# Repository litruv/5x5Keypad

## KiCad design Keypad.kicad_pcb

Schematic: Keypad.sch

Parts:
C1, C2: 22pF; C_0805_2012Metric_Pad1.15x1.40mm_HandSolder
C3, C5, C6, C7, C8, C9, C10, C11, C12, C13, C14, C15, C16: 0.1uF; C_0805_2012Metric_Pad1.15x1.40mm_HandSolder
C4: 1uF; C_0805_2012Metric_Pad1.15x1.40mm_HandSolder
D4, D5, D6, D7, D8, D9, D10, D11, D12, D13, D14, D15: WS2812B; LED_WS2812B_PLCC4_5.0x5.0mm_P3.2mm
F1: Polyfuse; Fuse_1206_3216Metric_Pad1.42x1.75mm_HandSolder
J1: AVR-ISP-6; PinHeader_2x03_P2.54mm_Vertical
Q1: Q_NPN_BCE; SOT-223-3_TabPin2
R1: 10K; R_0805_2012Metric_Pad1.15x1.40mm_HandSolder
R3, R4: 22; R_0805_2012Metric_Pad1.15x1.40mm_HandSolder
R6: 1.5k; R_0805_2012Metric_Pad1.15x1.40mm_HandSolder
SW1: SW_Push; CandK_6x6mm_Tactile
TRRS1, TRRS2: AudioJack4_Ground; TRRS-PJ-320A
U1, U2, U3, U4, U5, U6, U7, U8, U9, U10, U12, U13, U14, U15, U16, U17, U18, U19, U20, U21, U22, U23, U24, U25, U26: MXDiode; HybridMatiasCMX
U11: ATmega32U4-AU; TQFP-44_10x10mm_P0.8mm
USB1: 12401598E4#2A
USB2: USB_B; USB_Micro-B_Wuerth_629105150521
Y1: 16MHz; Crystal_SMD_5032-2Pin_5.0x3.2mm_HandSoldering

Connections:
A0: U11.36 (PF7)
A1: U11.37 (PF6)
A2: U11.38 (PF5)
A3: U11.39 (PF4)
A4: U11.40 (PF1)
A5: U11.41 (PF0)
Backlight: R6.2, U11.29 (PB5)
Col0: U1.5, U6.5, U11.27 (PD7), U12.5, U17.5, U22.5
Col1: U2.5, U7.5, U11.1 (PE6), U13.5, U18.5, U23.5
Col2: U3.5, U8.5, U11.20 (PD2), U14.5, U19.5, U24.5
Col3: U4.5, U9.5, U11.21 (PD3), U15.5, U20.5, U25.5
Col4: U5.5, U10.5, U11.25 (PD4), U16.5, U21.5, U26.5
D+: R3.2, USB1.A6, USB1.B6, USB2.3
D-: R4.2, USB1.A7, USB1.B7, USB2.2
LEDGnd: Q1.2, U1.3, U2.3, U3.3, U4.3, U5.3, U6.3, U7.3, U8.3, U9.3, U10.3, U12.3, U13.3, U14.3, U15.3, U16.3, U17.3, U18.3, U19.3, U20.3, U21.3, U22.3, U23.3, U24.3, U25.3, U26.3
LedStrip: D4.4, U11.26 (PD6)
MOSI: J1.4, U11.10 (PB2)
MSIO: J1.1, U11.11 (PB3)
unnamed: C1.1, U11.17 (XTAL1), Y1.1
unnamed: C2.2, U11.16 (XTAL2), Y1.2
unnamed: C3.2, U11.42 (AREF)
unnamed: C4.2, U11.6 (UCAP)
unnamed: D4.2, D5.4
unnamed: D5.2, D6.4
unnamed: D6.2, D7.4
unnamed: D7.2, D8.4
unnamed: D8.2, D9.4
unnamed: D10.2, D11.4
unnamed: D9.2, D10.4
unnamed: D11.2, D12.4
unnamed: D12.2, D13.4
unnamed: D13.2, D14.4
unnamed: D14.2, D15.4
unnamed: F1.2, USB1.A4, USB1.A9, USB1.B4, USB1.B9, USB2.1
unnamed: Q1.1, R6.1
unnamed: R3.1, U11.4 (D+)
unnamed: R4.1, U11.3 (D-)
RST: J1.5, R1.1, SW1.2, U11.13 (~RESET)
Row0: U1.1, U2.1, U3.1, U4.1, U5.1, U11.28 (PB4)
Row1: U6.1, U7.1, U8.1, U9.1, U10.1, U11.30 (PB6)
Row2: U11.12 (PB7), U12.1, U13.1, U14.1, U15.1, U16.1
Row3: U11.31 (PC6), U17.1, U18.1, U19.1, U20.1, U21.1
Row4: U11.32 (PC7), U22.1, U23.1, U24.1, U25.1, U26.1
SCK: J1.3, U11.9 (PB1)
SCL: TRRS1.1, TRRS2.1, U11.18 (PD0)
SDA: TRRS1.2, TRRS2.2, U11.19 (PD1)
UVCC: C5.1, C6.1, C7.1, C8.1, C9.1, C10.1, C11.1, C12.1, C13.1, C14.1, C15.1, C16.1, D4.1, D5.1, D6.1, D7.1, D8.1, D9.1, D10.1, D11.1, D12.1, D13.1, D14.1, D15.1, F1.1, J1.2, R1.2, TRRS1.3, TRRS2.3, U1.4, U2.4, U3.4, U4.4, U5.4, U6.4, U7.4, U8.4, U9.4, U10.4, U11.2 (UVCC), U11.7 (VBUS), U11.14 (VCC), U11.24 (AVCC), U11.34 (VCC), U11.44 (AVCC), U12.4, U13.4, U14.4, U15.4, U16.4, U17.4, U18.4, U19.4, U20.4, U21.4, U22.4, U23.4, U24.4, U25.4, U26.4

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
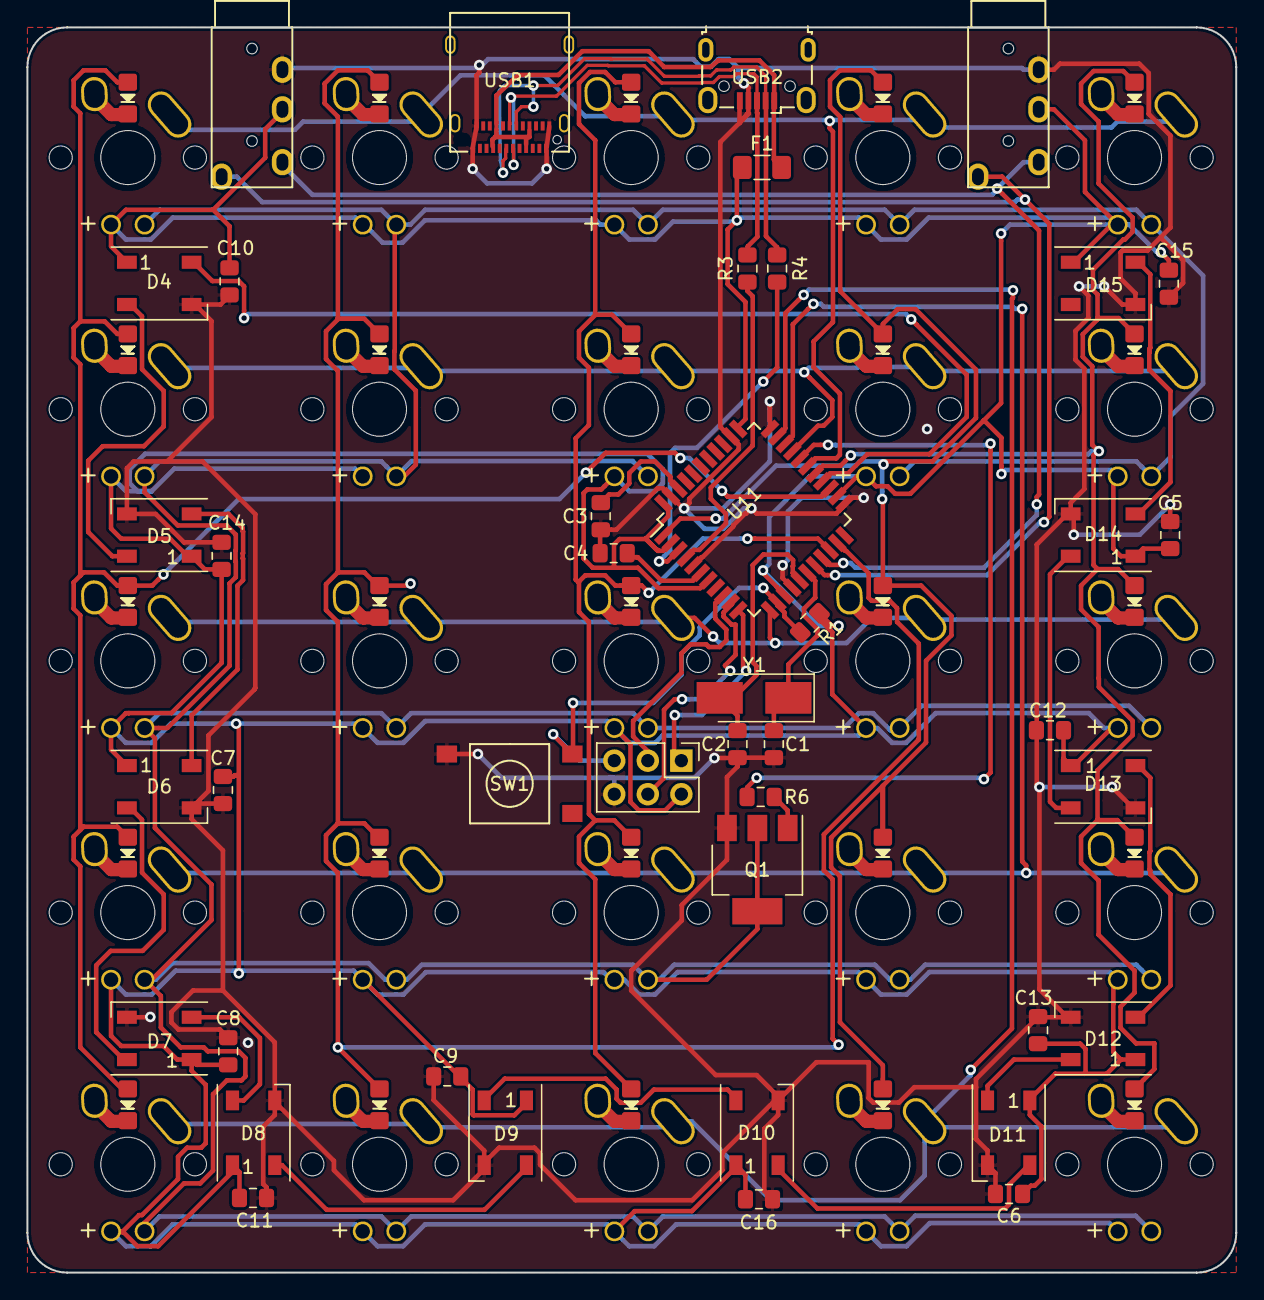
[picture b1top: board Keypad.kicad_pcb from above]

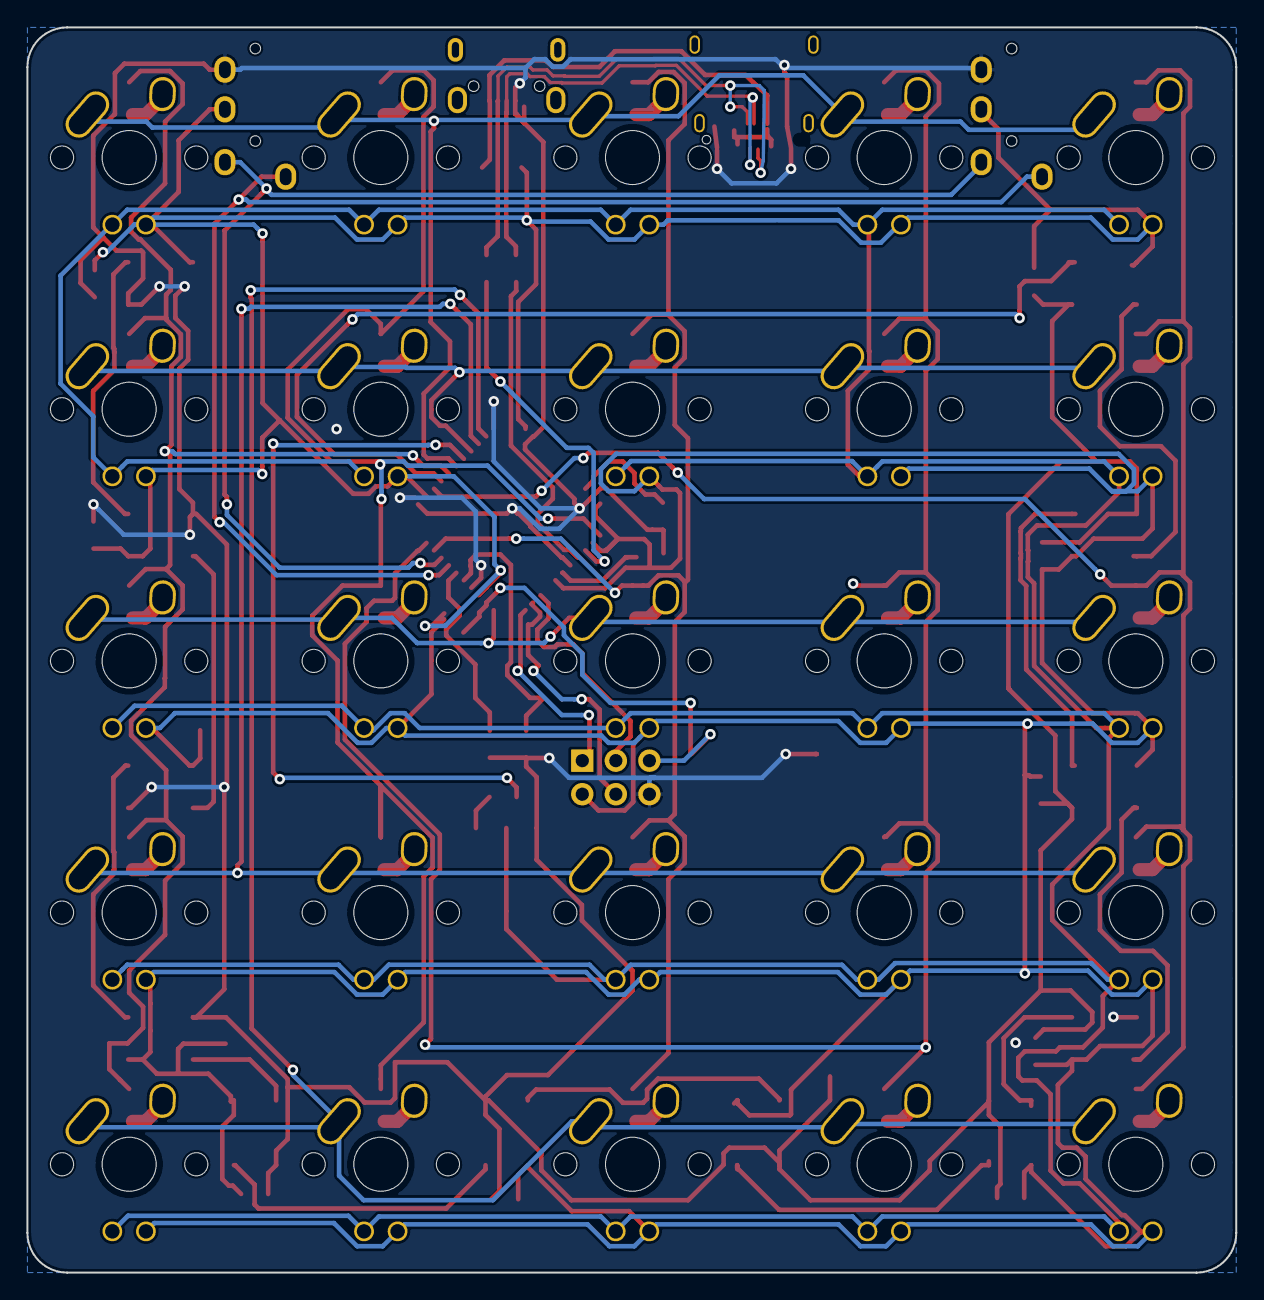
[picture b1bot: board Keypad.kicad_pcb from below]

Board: 2 copper layers, 91.5 x 94.2 mm, 67 parts (25 on the bottom side), 42 nets.

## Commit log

2018-09-01 Added PCB + Schematic
    Don't know if KiCAD supports schematic export correctly..
